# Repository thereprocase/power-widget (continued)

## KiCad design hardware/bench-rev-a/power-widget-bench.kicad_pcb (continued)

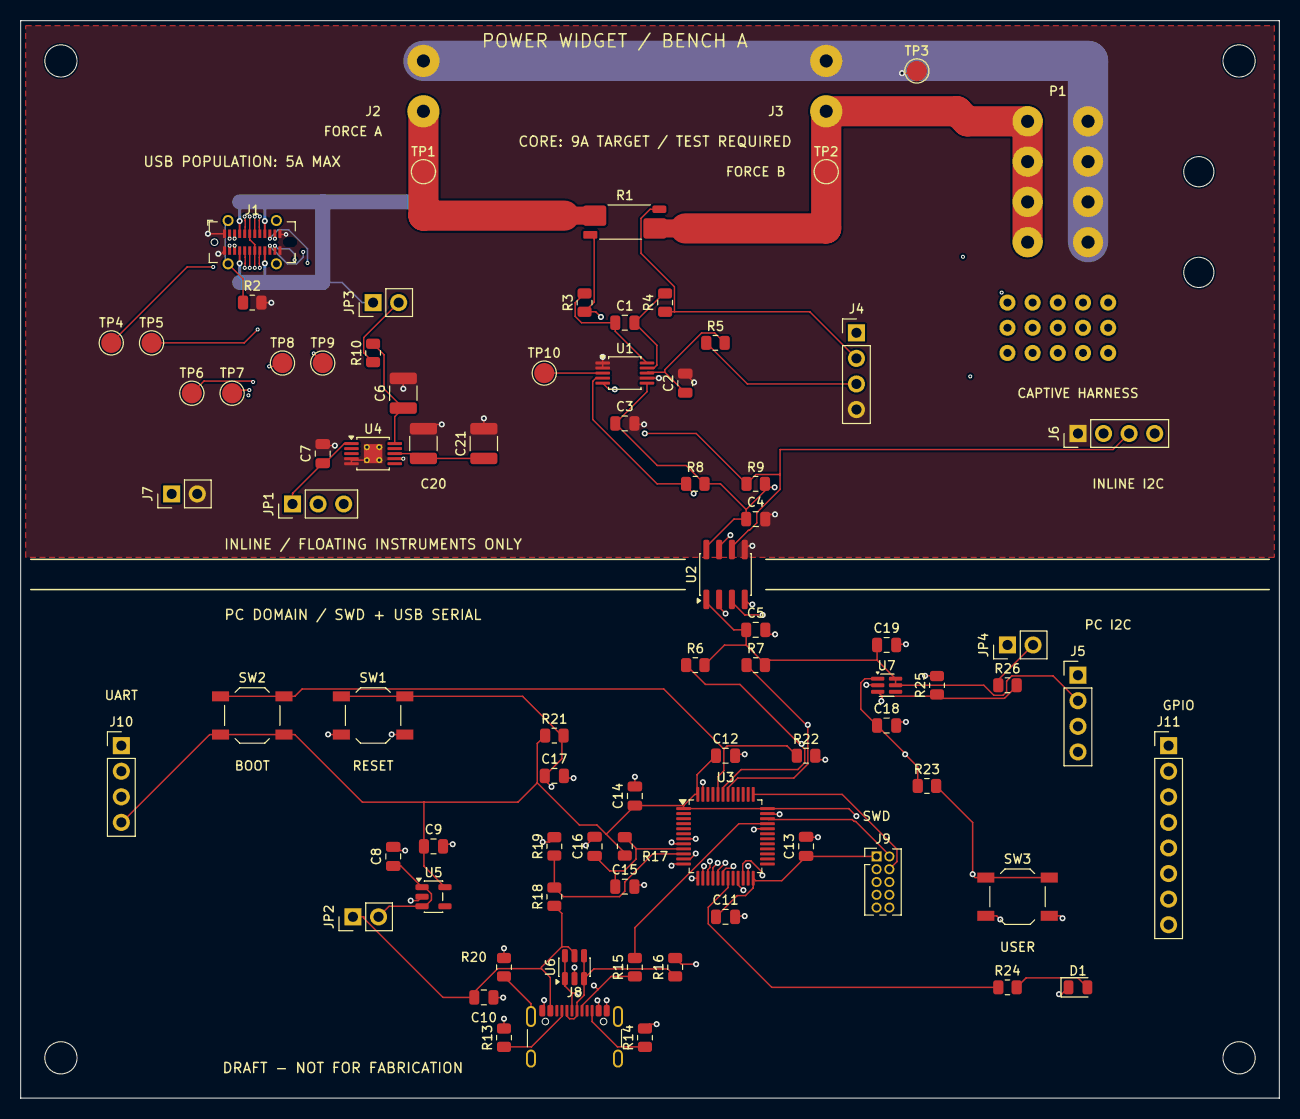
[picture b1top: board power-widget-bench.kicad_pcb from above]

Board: 4 copper layers, 125.0 x 107.0 mm, 88 parts (0 on the bottom side), 65 nets.

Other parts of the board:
H99, H1269, H9108, H126108: MountingHole_3.2mm
H12220, H12230: StrainRelief_3mm

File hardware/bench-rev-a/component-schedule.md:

# Bench component schedule

**Exported from the canonical native KiCad schematic. Draft, not an orderable BOM.**
The group column is a functional placement group, not a separate schematic sheet.

| Reference | Value / candidate | Domain | Group |
|---|---|---|---|
| C1 | 100nF 100V differential | INLINE | 02-sensing |
| C2 | 10nF 100V X7R | INLINE | 02-sensing |
| C3 | 100nF 10V at U1 | INLINE | 02-sensing |
| C4 | 100nF 10V at U2.8 | INLINE | 02-sensing |
| C5 | 100nF 10V at U2.1 | PC | 02-sensing |
| C6 | 1uF 100V X7R | INLINE | 03-supplies |
| C7 | 2u2 10V X7R | INLINE | 03-supplies |
| C8 | 1uF 10V | PC | 03-supplies |
| C9 | 4u7 10V | PC | 03-supplies |
| C10 | 1uF 10V at connector | PC | 03-supplies |
| C11 | 100nF 10V at U3.24 | PC | 04-usb-mcu |
| C12 | 100nF 10V at U3.48 | PC | 04-usb-mcu |
| C13 | 100nF 10V at U3.36 | PC | 04-usb-mcu |
| C14 | 100nF 10V at U3.1 | PC | 04-usb-mcu |
| C15 | 100nF 10V at U3.9 | PC | 04-usb-mcu |
| C16 | 1uF 10V | PC | 04-usb-mcu |
| C17 | 100nF reset | PC | 05-debug |
| C18 | 100nF 10V at U7.1 | PC | 03-supplies |
| C19 | 1uF 10V at U7.6 | PC | 03-supplies |
| C20 | 22uF 50V X7R MID | INLINE | 03-supplies |
| C21 | 22uF 50V X7R MID | INLINE | 03-supplies |
| D1 | Activity LED | PC | 05-debug |
| J1 | USB4115-03-C / USB path 5A MAX | INLINE | 01-inline |
| J2 | 691137710002 / force terminal | INLINE | 01-inline |
| J3 | 691137710002 / force terminal | INLINE | 01-inline |
| J4 | Kelvin probe pads; NOT force pins | INLINE | 01-inline |
| J5 | PC I2C / external MCU | PC | 02-sensing |
| J6 | INLINE I2C debug | INLINE | 02-sensing |
| J7 | Floating external 3.3V | INLINE | 03-supplies |
| J8 | USB4105-GF-A-120 / reporting | PC | 04-usb-mcu |
| J9 | Cortex SWD 2x5 1.27mm | PC | 05-debug |
| J10 | UART 3.3V logic | PC | 05-debug |
| J11 | Spare GPIO / SPI | PC | 05-debug |
| JP1 | SENSOR SUPPLY: one shunt only | INLINE | 03-supplies |
| JP2 | PC supply current link | PC | 03-supplies |
| JP3 | INLINE self-current link | INLINE | 03-supplies |
| JP4 | External-master enable; DNF | PC | 03-supplies |
| P1 | Captive harness solder termination | INLINE | 01-inline |
| R1 | WSK25125L000DEA / 5mR 1W | INLINE | 01-inline |
| R2 | 0R shield bond | INLINE | 01-inline |
| R3 | 10R 0.1% matched | INLINE | 02-sensing |
| R4 | 10R 0.1% matched | INLINE | 02-sensing |
| R5 | 100R | INLINE | 02-sensing |
| R6 | 2k2 pull-up | PC | 02-sensing |
| R7 | 2k2 pull-up | PC | 02-sensing |
| R8 | 2k2 pull-up | INLINE | 02-sensing |
| R9 | 2k2 pull-up | INLINE | 02-sensing |
| R10 | 10R 0.25W branch feed | INLINE | 03-supplies |
| R13 | 5k1 1% Rd | PC | 04-usb-mcu |
| R14 | 5k1 1% Rd | PC | 04-usb-mcu |
| R15 | 0R tuning footprint | PC | 04-usb-mcu |
| R16 | 0R tuning footprint | PC | 04-usb-mcu |
| R17 | 10R VDDA filter | PC | 04-usb-mcu |
| R18 | 100k 1% | PC | 04-usb-mcu |
| R19 | 100k 1% | PC | 04-usb-mcu |
| R20 | 0R PC shell bond | PC | 04-usb-mcu |
| R21 | 10k reset pull-up | PC | 05-debug |
| R22 | 10k boot pull-down | PC | 05-debug |
| R23 | 10k button pull-up | PC | 05-debug |
| R24 | 1k LED limiter | PC | 05-debug |
| R25 | 100k enable pull-down | PC | 03-supplies |
| R26 | 10k override limiter | PC | 03-supplies |
| SW1 | RESET pushbutton | PC | 05-debug |
| SW2 | BOOT pushbutton | PC | 05-debug |
| SW3 | USER pushbutton | PC | 05-debug |
| TP1 | VBUS_A | INLINE | 01-inline |
| TP2 | VBUS_B | INLINE | 01-inline |
| TP3 | GND_INLINE | INLINE | 01-inline |
| TP4 | CONTACT_A5 | INLINE | 01-inline |
| TP5 | CONTACT_B5 | INLINE | 01-inline |
| TP6 | INLINE_DP | INLINE | 01-inline |
| TP7 | INLINE_DM | INLINE | 01-inline |
| TP8 | CONTACT_A8 | INLINE | 01-inline |
| TP9 | CONTACT_B8 | INLINE | 01-inline |
| TP10 | ALERT: floating scope only | INLINE | 02-sensing |
| U1 | INA228AIDGSR | INLINE | 02-sensing |
| U2 | ISO1641BD | BARRIER | 02-sensing |
| U3 | STM32F072CBT6 / 128K flash | PC | 04-usb-mcu |
| U4 | TPS7A4333DGQR | INLINE | 03-supplies |
| U5 | TLV75533PDBVR | PC | 03-supplies |
| U6 | USBLC6-2SC6 | PC | 04-usb-mcu |
| U7 | TPS22919DCKR | PC | 03-supplies |

## Assembly notes

- **J1:** 24 contacts, 48 V / 5 A manufacturer rating. This bench population is limited to 5 A via USB; a 9 A assembly remains a procurement gate.
- **J2:** Wurth 16 A UL / 24 A VDE, 5.00 mm pitch, 1.30 mm drills. Force path capacity still requires PCB thermal testing.
- **J3:** Wurth 16 A UL / 24 A VDE, 5.00 mm pitch, 1.30 mm drills. Force path capacity still requires PCB thermal testing.
- **J4:** Use small pads near the defined B-plane. No main current through this header.
- **J5:** 3V3 is switched reference/output. Hold onboard MCU in reset and fit JP4 for another open-drain master; no external pull-ups to an always-on rail.
- **J6:** Only a floating or isolated instrument here; never jumper to J5.
- **J7:** For zero-VBUS/low-voltage bench testing; not connected to PC supply.
- **J8:** Long board edge. USB 2.0 receptacle may omit unused SS/SBU contacts after exact footprint selection.
- **J9:** Key pin 7 absent. No SWO on Cortex-M0. Debug probe must not power this board.
- **J10:** TX/RX named from board viewpoint; 3V3 reference only. Not RS-232 voltage levels.
- **JP1:** Normal 1-2; floating external 3.3 V 2-3. Do not install two shunts.
- **JP2:** Fit shunt normally. Remove to measure reporting-domain supply current; no external power injection.
- **JP3:** Fit shunt normally; insert a floating ammeter to characterize sensor-side self-consumption. Not a main-current connection.
- **JP4:** Fit only for external-master bench use with U3 held reset; remove for USB suspend testing.
- **P1:** Board-side termination, not a USB mating footprint. Candidate USB4155-03-C plug is 48 V / 5 A only; custom harness drawing/qualification remains open.
- **R1:** Project pad numbering 1=I1, 2=I2, 3=E1, 4=E2. 5 mOhm uses T=1.19 mm termination variant; current pads and Kelvin pads mapped from Vishay drawing.
- **TP10:** No pull-up fitted; open drain requires a local pull-up if probing logic. Firmware polls status.
- **U1:** Address 0x40. Wide ADC range. Footprint candidate still requires package drawing review.
- **U2:** Side 1 PC, side 2 inline. SCL is unidirectional; INA228 does not require clock stretching.
- **U3:** Pinout checked against ST DS9826 Rev 6 figure 8. 16 KB RAM. HSI48/CRS USB clock.
- **U4:** 85 V fixed 3.3 V regulator. EN intentionally floating per internal pull-up; never tie EN to high VBUS. MID selected 15 V, with capacitors sized >=3x total OUT capacitance.
- **U6:** Route lines through paired pads with short ground return. PC port only.
- **U7:** Switch U2 side 1 and its pull-ups off in USB suspend. Set PB6/PB7 high impedance first. QOD tied to output.
